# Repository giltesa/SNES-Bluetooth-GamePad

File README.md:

# SNES Bluetooth GamePad

This project was **cancelled**. It contains some files of when I tried to make a Bluetooth gamepad using a Bluetooth keyboard components in 2013.

You can get more information here:

[**Blog**](https://giltesa.com/category/electronica/mas-electronica/snes-gamepad-bluetooth).

## License

This project is licensed under a **Creative Commons** license:
**[Attribution-NonCommercial-ShareAlike 4.0 International (CC BY-NC-SA 4.0) ](https://creativecommons.org/licenses/by-nc-sa/4.0/)**

Check the [LICENSE.md](LICENSE.md) for more information.

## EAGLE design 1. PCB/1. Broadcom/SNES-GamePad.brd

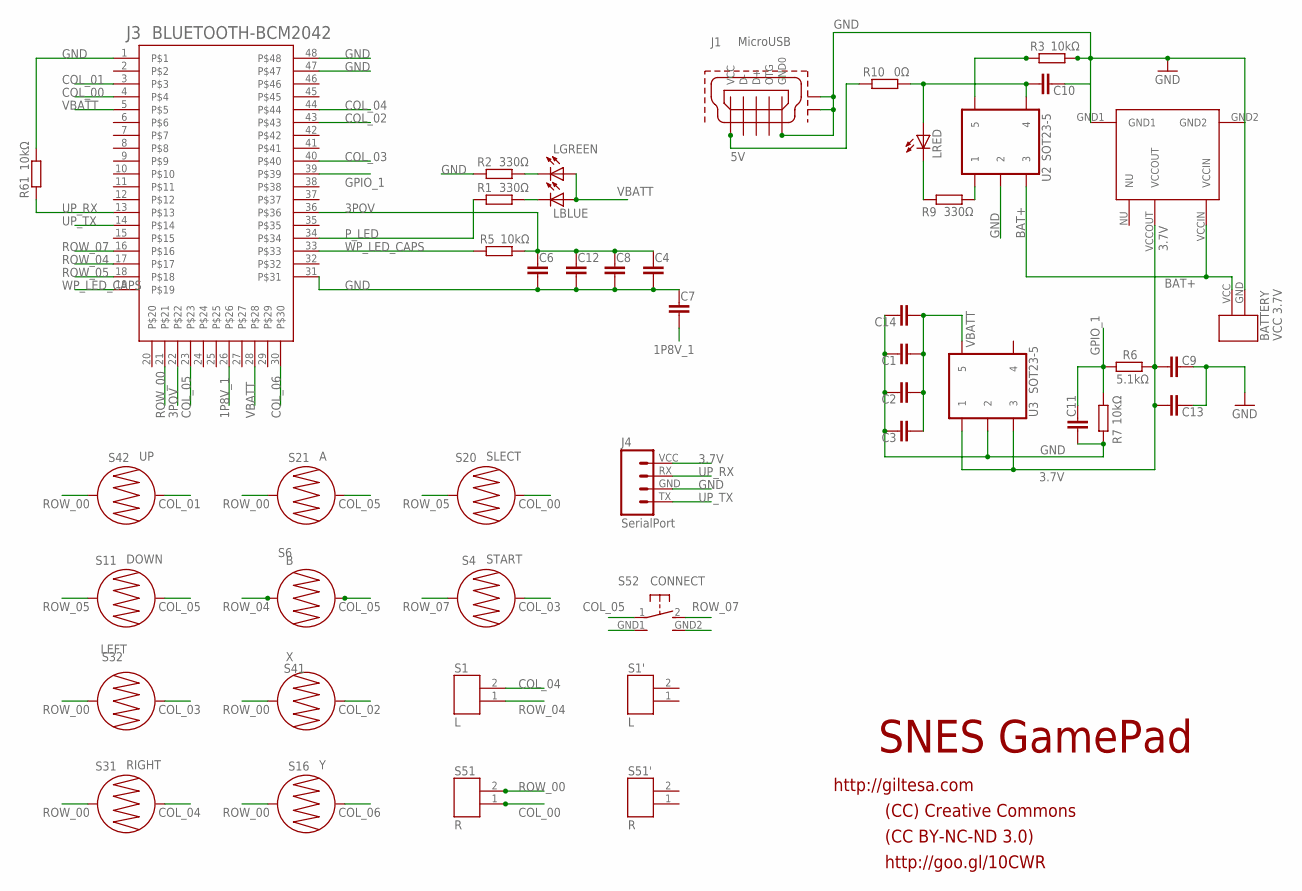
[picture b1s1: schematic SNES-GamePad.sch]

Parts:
BATTERY: VCC 3.7V; 1X02_SMD_BIG
C1, C4, C10, C11: C-EUC0603; C0603
C2, C3, C6, C7, C8, C9, C12, C13, C14: C-EUC0805; C0805
J1: MicroUSB; MICRO_USB_1
J2: INTERRUPTOR_1
J3: BLUETOOTH-BCM2042
J4: SerialPort; ISP_PORT_SNES
LBLUE: LEDCHIPLED_0805; CHIPLED_0805
LGREEN: LEDCHIPLED_0805; CHIPLED_0805
LRED: LEDCHIPLED_0805; CHIPLED_0805
R1, R2, R9: 330Ω; R0603
R3, R5, R7, R61: 10kΩ; R0603
R6: 5.1kΩ; R0603
R10: 0Ω; R0603
S1: L; 1X02_SMD
S1': L; SNES_GAMEPAD_RL
S4: START; BUTTON-CONDUCTIVE-BUTTON
S6: B; BUTTON-CONDUCTIVE-BUTTON
S11: DOWN; BUTTON-CONDUCTIVE-PAD
S16: Y; BUTTON-CONDUCTIVE-BUTTON
S20: SLECT; BUTTON-CONDUCTIVE-BUTTON
S21: A; BUTTON-CONDUCTIVE-BUTTON
S31: RIGHT; BUTTON-CONDUCTIVE-PAD
S32: LEFT; BUTTON-CONDUCTIVE-PAD
S41: X; BUTTON-CONDUCTIVE-BUTTON
S42: UP; BUTTON-CONDUCTIVE-PAD
S51: R; 1X02_SMD
S51': R; SNES_GAMEPAD_RL
S52: CONNECT; SWITCH-90º
U2, U3: SOT23-5

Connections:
1P8V_1: C7.1, J3.26
3.7V: C9.2, C13.2, J2.VCCOUT, J4.VCC, R6.2, U3.1, U3.3
3POV: C4.1, C6.1, C8.1, C12.1, J3.22, J3.36, R5.2
5V: J1.VCC, R10.1
BAT+: BATTERY.VCC, J2.VCCIN, U2.3
COL_00: J3.4, S20.2, S51.1
COL_01: J3.3, S42.2
COL_02: J3.43, S41.1
COL_03: J3.40, S4.2, S32.1
COL_04: J3.44, S1.2, S31.2
COL_05: J3.23, S6.1, S11.2, S21.2, S52.1
COL_06: J3.30, S16.2
GND: BATTERY.GND, C1.1, C2.1, C3.1, C4.2, C6.2, C7.2, C8.2, C9.1, C10.2, C11.1, C12.2, C13.1, C14.1, J1.GND0, J1.GND1, J1.GND2, J2.GND1, J2.GND2, J3.1, J3.31, J3.47, J3.48, J4.GND, R2.1, R3.2, R7.1, R61.2, S52.GND1, S52.GND2, U2.2, U3.2
GPIO_1: C11.2, J3.39, R6.1, R7.2
unnamed: LBLUE.C, R1.2
unnamed: C10.1, LRED.A, R10.2, U2.4
unnamed: LRED.C, R9.2
unnamed: R3.1, U2.5
unnamed: LGREEN.C, R2.2
unnamed: R9.1, U2.1
P_LED: J3.34, R1.1
ROW_00: J3.21, S16.1, S21.1, S31.1, S32.2, S41.2, S42.1, S51.2
ROW_04: J3.17, S1.1, S6.2
ROW_05: J3.18, S11.1, S20.1
ROW_07: J3.16, S4.1, S52.2
UP_RX: J3.13, J4.RX, R61.1
UP_TX: J3.14, J4.TX
VBATT: C1.2, C2.2, C3.2, C14.2, J3.5, J3.28, LBLUE.A, LGREEN.A, U3.5
WP_LED_CAPS: J3.19, J3.33, R5.1

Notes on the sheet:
http://giltesa.com
(CC) Creative Commons
(CC BY-NC-ND 3.0)
http://goo.gl/10CWR
SNES GamePad

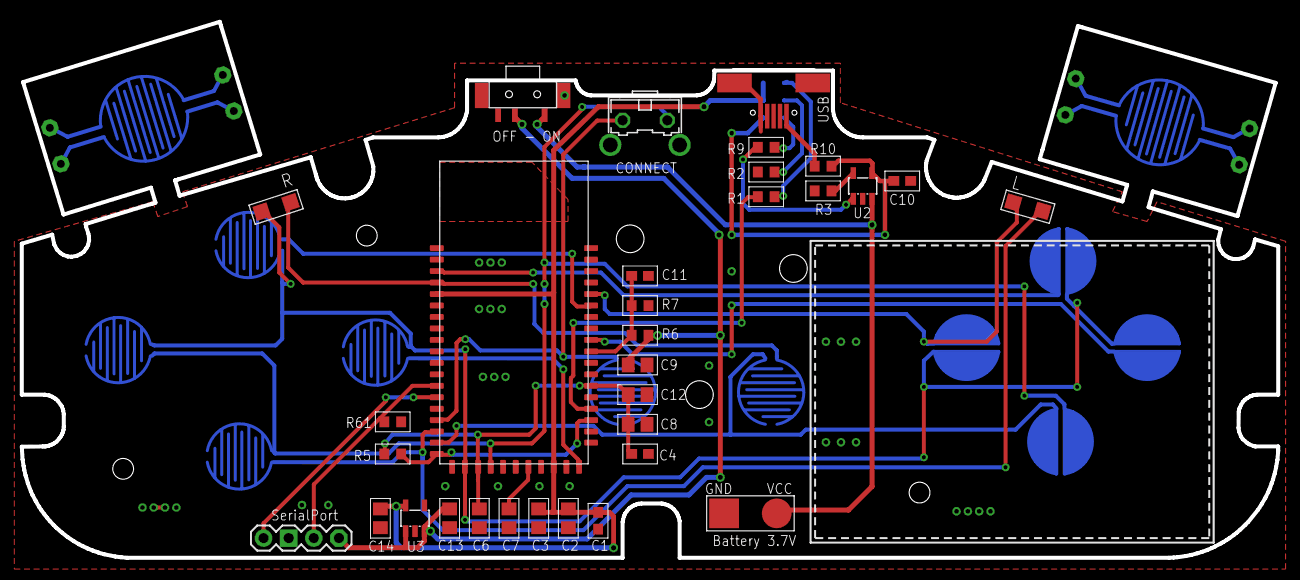
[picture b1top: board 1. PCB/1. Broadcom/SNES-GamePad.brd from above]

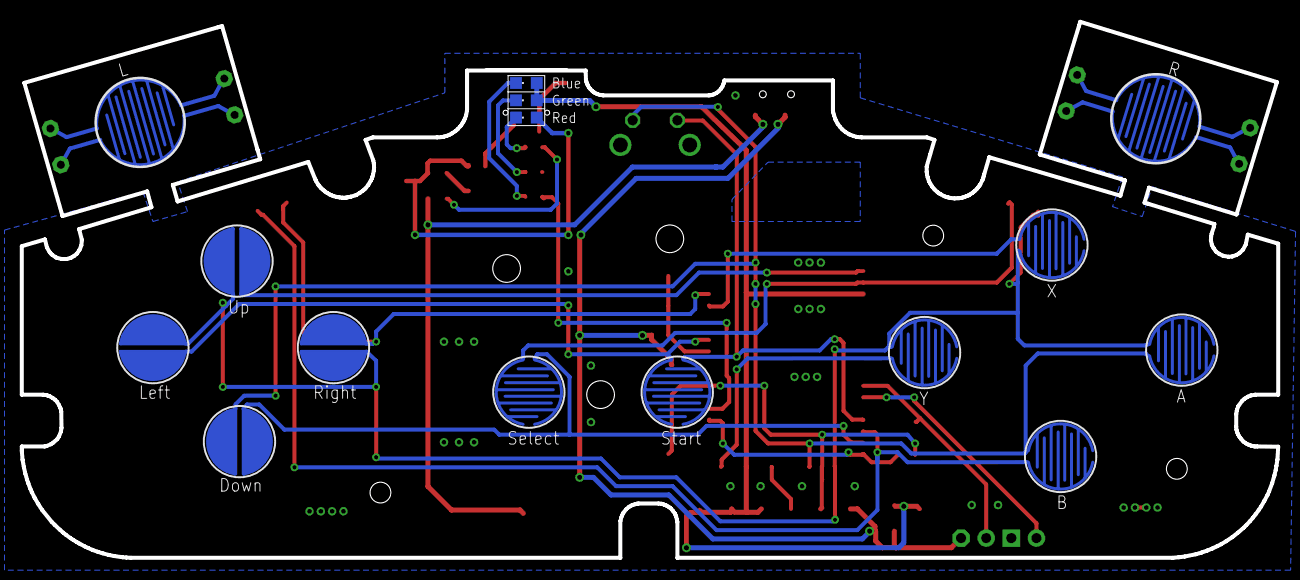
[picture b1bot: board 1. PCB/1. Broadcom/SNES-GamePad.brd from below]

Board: 2 copper layers, 127.0 x 54.2 mm, 47 parts (15 on the bottom side), 29 nets.

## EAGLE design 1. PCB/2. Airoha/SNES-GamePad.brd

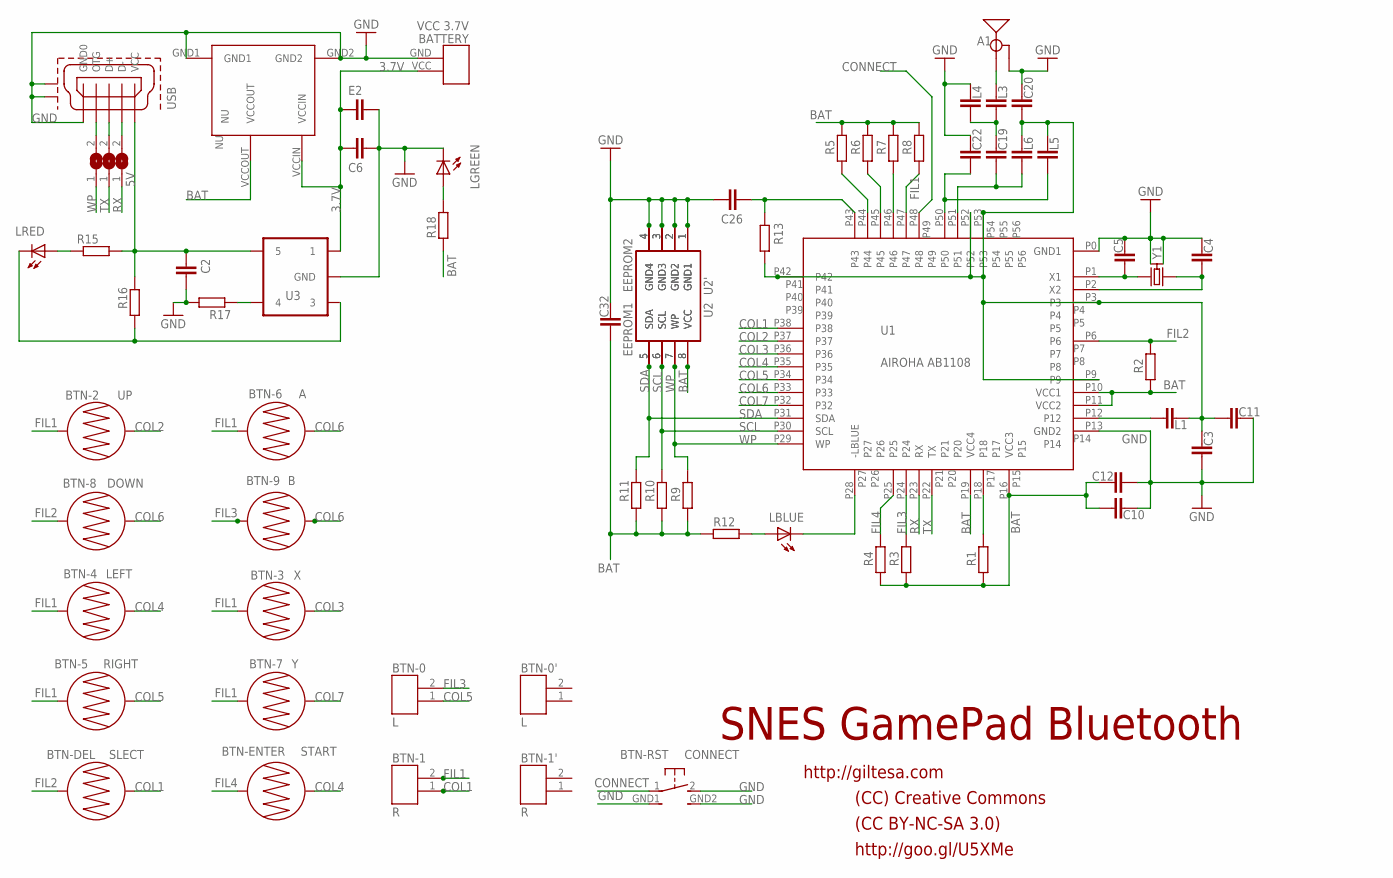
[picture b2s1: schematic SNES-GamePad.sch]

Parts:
A1: ANTENA; ANTENA-AIROHA
BATTERY: VCC 3.7V; 1X02_SMD_BIG
BTN-0: L; 1X02_SMD
BTN-0': L; SNES_GAMEPAD_RL
BTN-1: R; 1X02_SMD
BTN-1': R; SNES_GAMEPAD_RL
BTN-2: UP; BUTTON-CONDUCTIVE-PAD
BTN-3: X; BUTTON-CONDUCTIVE-BUTTON
BTN-4: LEFT; BUTTON-CONDUCTIVE-PAD
BTN-5: RIGHT; BUTTON-CONDUCTIVE-PAD
BTN-6: A; BUTTON-CONDUCTIVE-BUTTON
BTN-7: Y; BUTTON-CONDUCTIVE-BUTTON
BTN-8: DOWN; BUTTON-CONDUCTIVE-PAD
BTN-9: B; BUTTON-CONDUCTIVE-BUTTON
BTN-DEL: SLECT; BUTTON-CONDUCTIVE-BUTTON
BTN-ENTER: START; BUTTON-CONDUCTIVE-BUTTON
BTN-RST: CONNECT; SWITCH-90º
C2, C3, C4, C5, C6, C10, C11, C12, C19, C20, C22, C26, C32: C0603
E2: C0805
L1: C1206
L3, L4, L5, L6: C0603
LBLUE: LEDCHIPLED_0805; CHIPLED_0805
LGREEN: LEDCHIPLED_0805; CHIPLED_0805
LRED: LEDCHIPLED_0805; CHIPLED_0805
R1, R2, R3, R4, R5, R6, R7, R8: 22kΩ; R0603
R9, R17: 4.7kΩ; R0603
R10, R11: 2.2kΩ; R0603
R12, R15: 330Ω; R0603
R13: 10Ω; R0603
R16: 10kΩ; R0603
R18: 1kΩ; R0603
S2: INTERRUPTOR_1
SJ1, SJ2, SJ3: JUMPER-SMD
U1: AIROHA AB1108; QFN56_6MM
U2: EEPROM1; TSSOP8
U2': EEPROM2; M8-EEPROM
U3: SOT23-5
USB: MICRO_USB_1
Y1: CRISTAL; CRISTAL-SMD-3X2.5MM

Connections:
3.7V: BATTERY.VCC, C6.1, E2.1, S2.VCCIN, U3.1
5V: C2.1, R15.2, R16.2, U3.5, USB.VCC
BAT: C10.1, C12.1, C32.2, R1.1, R2.1, R3.1, R4.1, R5.2, R6.2, R7.2, R8.2, R9.1, R10.1, R11.1, R12.1, R18.2, S2.VCCOUT, U1.P10 (VCC1), U1.P11 (VCC2), U1.P16 (VCC3), U1.P19 (VCC4), U2.8 (VCC), U2'.8 (VCC)
COL1: BTN-1.1, BTN-DEL.2, U1.P38
COL2: BTN-2.2, U1.P37
COL3: BTN-3.1, U1.P36
COL4: BTN-4.1, BTN-ENTER.1, U1.P35
COL5: BTN-0.1, BTN-5.2, U1.P34
COL6: BTN-6.2, BTN-8.2, BTN-9.2, U1.P33
COL7: BTN-7.2, U1.P32
CONNECT: BTN-RST.1, U1.P48
FIL1: BTN-1.2, BTN-2.1, BTN-3.2, BTN-4.2, BTN-5.1, BTN-6.1, BTN-7.1, R8.1, U1.P47
FIL2: BTN-8.1, BTN-DEL.1, R2.2, U1.P6
FIL3: BTN-0.2, BTN-9.1, R3.2, U1.P24
FIL4: BTN-ENTER.2, R4.2, U1.P25
GND: A1.GND, BATTERY.GND, BTN-RST.2, BTN-RST.GND1, BTN-RST.GND2, C2.2, C3.2, C4.1, C5.1, C6.2, C10.2, C11.1, C12.2, C20.1, C22.1, C26.2, C32.1, E2.2, L4.1, LGREEN.C, R17.2, S2.GND1, S2.GND2, U1.P0 (GND1), U1.P13 (GND2), U2.1 (GND1), U2.2 (GND2), U2.3 (GND3), U2.4 (GND4), U2'.1 (GND1), U2'.2 (GND2), U2'.3 (GND3), U2'.4 (GND4), U3.2 (GND), USB.GND0, USB.GND1, USB.GND2, Y1.GND1, Y1.GND2
unnamed: LRED.A, R15.1
unnamed: C22.2, L5.2, U1.P50
unnamed: SJ1.2, USB.OTG
unnamed: LGREEN.A, R18.1
unnamed: C19.1, L3.2, L4.2
unnamed: A1.SIGNAL, L3.1
unnamed: C19.2, L6.2, U1.P51
unnamed: SJ3.2, USB.D-
unnamed: SJ2.2, USB.D+
unnamed: LBLUE.C, U1.P28 (-LBLUE)
unnamed: LRED.C, R16.1, U3.3
unnamed: R17.1, U3.4
unnamed: LBLUE.A, R12.2
unnamed: C26.1, R13.1, U1.P43
unnamed: C3.1, C11.2, C20.2, L1.2, L5.1, L6.1, R13.2, U1.P3, U1.P9, U1.P42, U1.P52, U1.P53
unnamed: R1.2, U1.P18
unnamed: R5.1, U1.P44
unnamed: R6.1, U1.P45
unnamed: R7.1, U1.P46
unnamed: L1.1, U1.P12
RX: SJ3.1, U1.P23 (RX)
SCL: R10.2, U1.P30 (SCL), U2.6 (SCL), U2'.6 (SCL)
SDA: R11.2, U1.P31 (SDA), U2.5 (SDA), U2'.5 (SDA)
TX: SJ2.1, U1.P22 (TX)
WP: R9.2, SJ1.1, U1.P29 (WP), U2.7 (WP), U2'.7 (WP)
X1: C5.2, U1.P1 (X1), Y1.P2
X2: C4.2, U1.P2 (X2), Y1.P1

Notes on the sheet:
http://giltesa.com
(CC) Creative Commons
(CC BY-NC-SA 3.0)
http://goo.gl/U5XMe
SNES GamePad Bluetooth

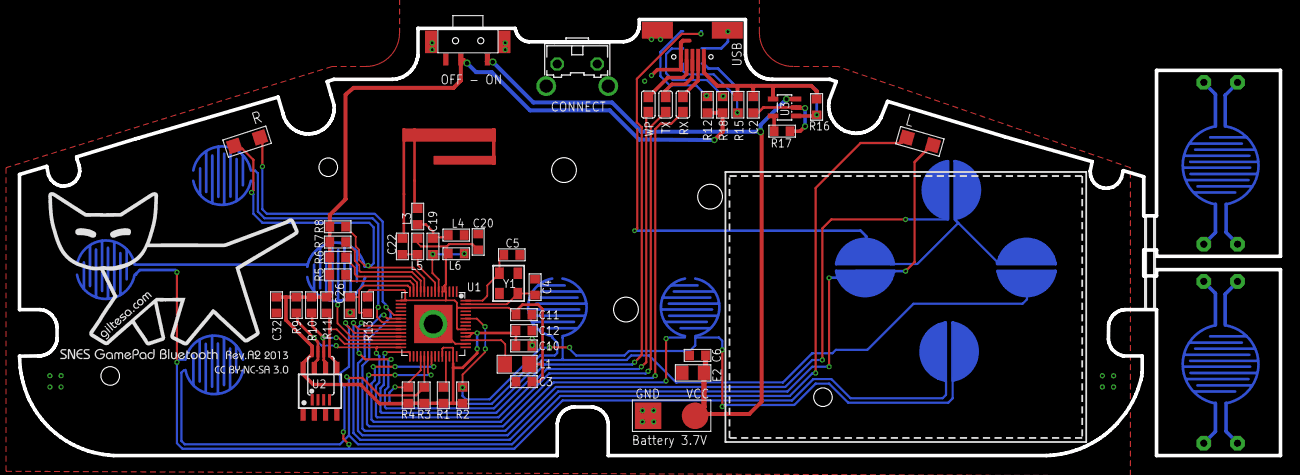
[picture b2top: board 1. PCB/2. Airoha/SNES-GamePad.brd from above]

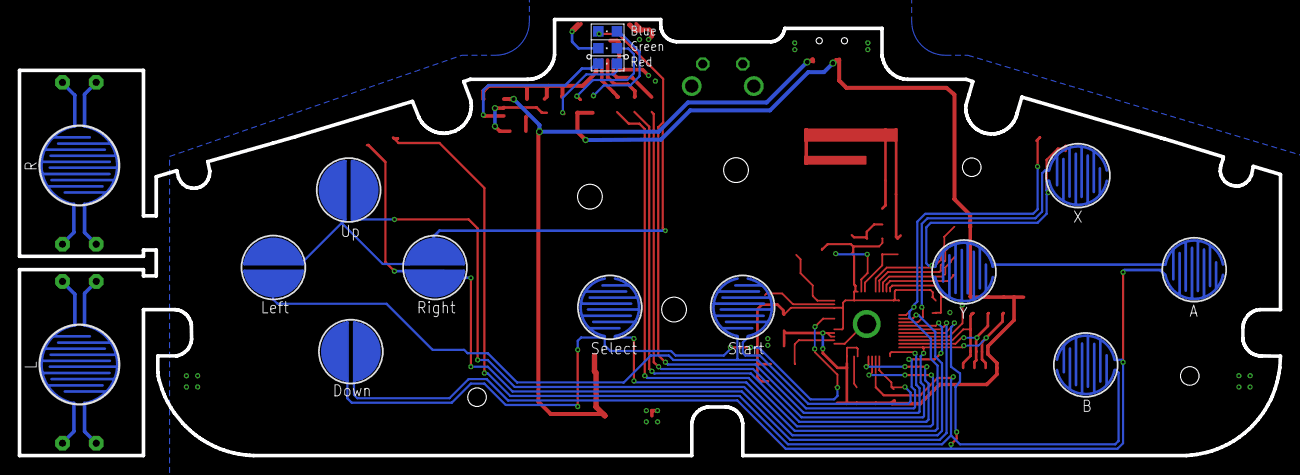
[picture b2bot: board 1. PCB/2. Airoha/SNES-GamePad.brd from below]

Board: 2 copper layers, 142.4 x 49.3 mm, 67 parts (15 on the bottom side), 43 nets.

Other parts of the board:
U$1: SNES-LOGO

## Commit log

2021-02-18 Rev2 (Cancelled)
